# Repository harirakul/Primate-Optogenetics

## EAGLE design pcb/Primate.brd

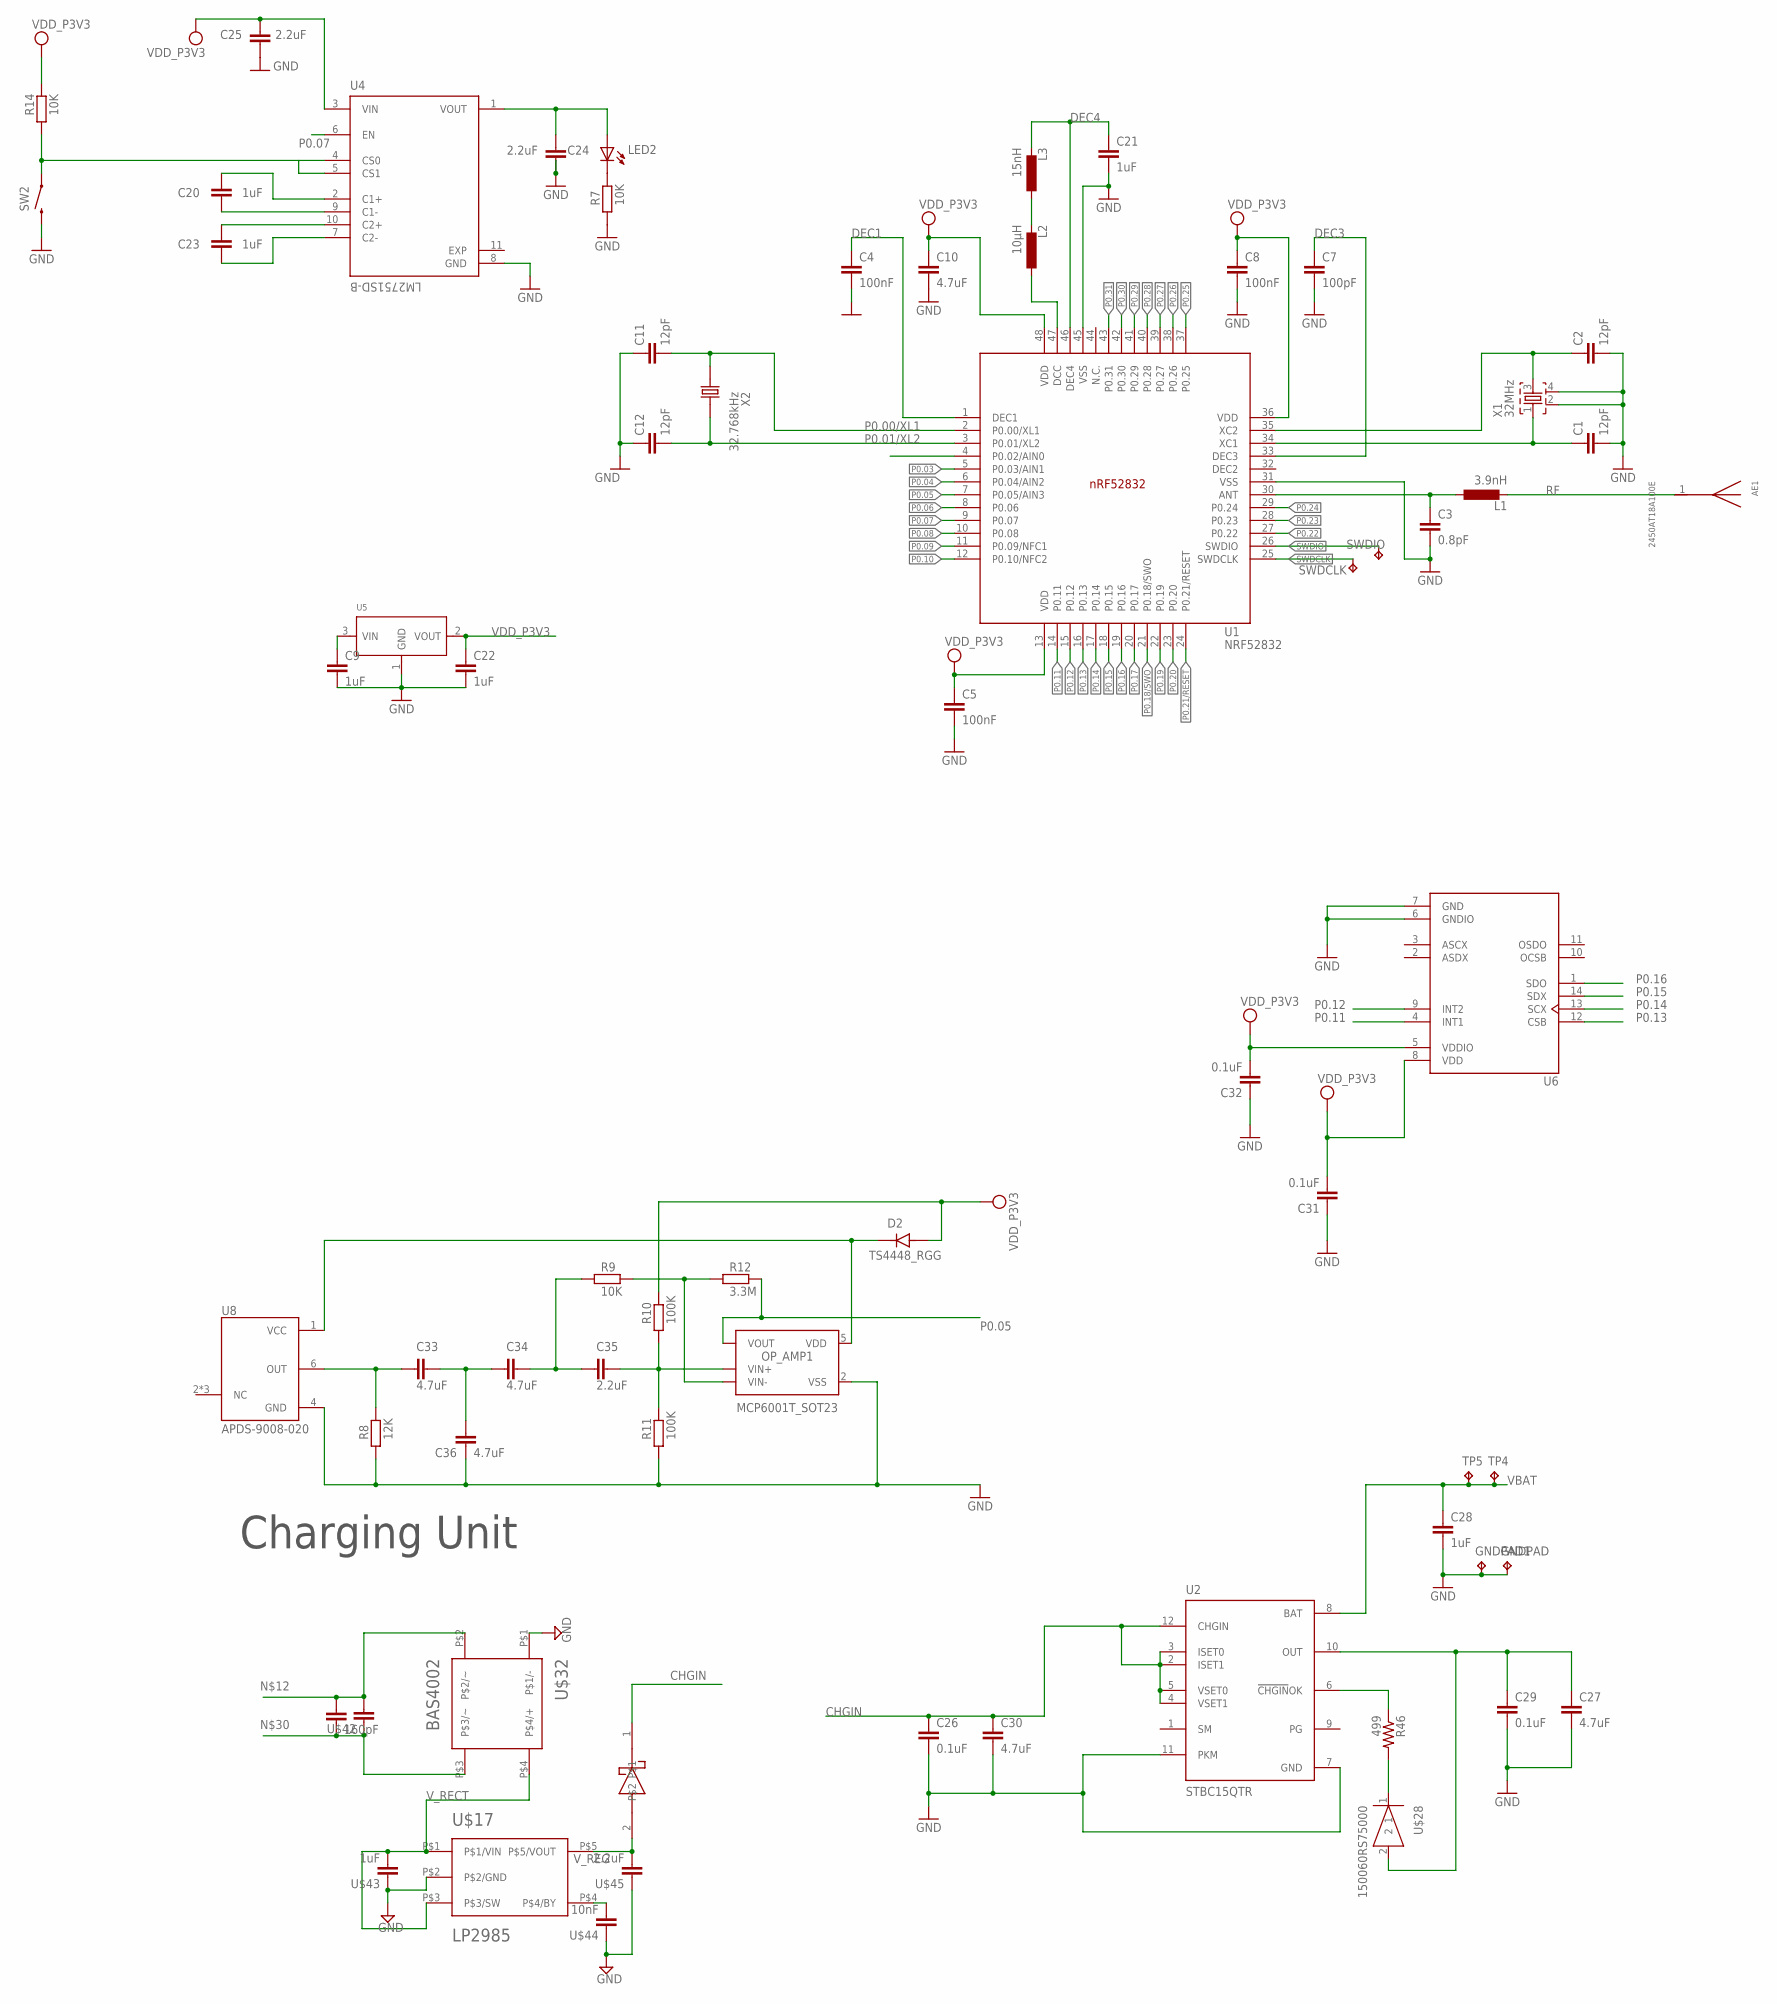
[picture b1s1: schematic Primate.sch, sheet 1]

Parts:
AE1: 2450AT18A100E; ANTC3216X140N
C1, C2, C11, C12: 12pF; C0201
C3: 0.8pF; C0201
C4, C5, C8: 100nF; C0201
C7: 100pF; C0201
C9, C20, C21, C22, C23, C28: 1uF; C0201
C10, C27, C30, C33, C34, C36: 4.7uF; C0402
C24, C25, C35: 2.2uF; C0402
C26, C29, C31, C32: 0.1uF; C0201
D2: TS4448_RGG; DIO_TS4448_RGG
GNDPAD, GNDPAD1: TPTP20SQ; TP20SQ
L1: 3.9nH; L0201
L2: 10µH; L0201
L3: 15nH; L0201
LED2: LEDCHIPLED_0805; CHIPLED_0805
OP_AMP1: MCP6001T_SOT23; SOT95P280X145-5N
R7, R9, R14: 10K; R0603
R8: 12K; R0603
R10, R11: 100K; R0603
R12: 3.3M; R0603
R46: 499; R0201
SW2: RS032G05A3SM-SPST-MOMENTARY-SWSMD-1101NE; TACTILE-SWITCH-1101NE
SWDCLK: TPB1,27; B1,27
SWDIO: TPB1,27; B1,27
TP4, TP5: TPTP20SQ; TP20SQ
U1: NRF52832; QFN40P600X600X90-48_N
U2: STBC15QTR; QFN40P200X170X55-12N
U4: LM2751SD-B; SON50P300X300X80-11N
U5: PMIC-LDO-XC6206P302MR(SOT23); SOT-23
U6: BMI160; PQFN50P250X300X88-14N
U8: APDS-9008-020; XDCR_APDS-9008-020
U$17: LP2985; SOT-23
U$28: 150060RS75000
U$32: BAS4002; SOT143
U$41: 160pF; C0201
U$42: 5pF; C0201
U$43: 1uF; C0201
U$44: 10nF; C0201
U$45: 2.2uF; C0201
U$46: CDBQC0130L-HF; 0402DIODE
X1: 32MHz; BT-XTAL_2016_N
X2: 32.768kHz; XTAL_ECS-.327-7-12-TR

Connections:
ANT: C3.1, L1.1, U1.30 (ANT)
CHGIN: C26.1, C30.1, U2.2 (ISET1), U2.3 (ISET0), U2.4 (VSET1), U2.5 (VSET0), U2.12 (CHGIN), U$46.1
DEC1: C4.1, U1.1 (DEC1)
DEC3: C7.1, U1.33 (DEC3)
DEC4: C21.1, L3.2, U1.46 (DEC4)
EXP: U4.11 (EXP)
GND: C1.2, C2.2, C3.2, C4.2, C5.2, C7.2, C8.2, C9.2, C10.2, C11.1, C12.1, C21.2, C22.2, C24.2, C25.2, C26.2, C27.2, C28.2, C29.2, C30.2, C31.1, C32.1, C36.2, GNDPAD.TP, GNDPAD1.TP, OP_AMP1.2 (VSS), R7.1, R8.1, R11.1, SW2.2, U1.31 (VSS), U1.45 (VSS), U2.7 (GND), U2.11 (PKM), U4.8 (GND), U5.1 (GND), U6.6 (GNDIO), U6.7 (GND), U8.4 (GND), U$17.P$2 (P$2/GND), U$32.P$1 (P$1/-), U$43.1, U$44.1, U$45.1, X1.2, X1.4
unnamed: L2.2, L3.1
unnamed: C2.1, U1.35 (XC2), X1.3
unnamed: L2.1, U1.47 (DCC)
unnamed: U$32.P$2 (P$2/~), U$41.1, U$42.2
unnamed: R46.2, U$28.1
unnamed: C33.2, R8.2, U8.6 (OUT)
unnamed: C27.1, C29.1, U2.10 (OUT), U$28.2
unnamed: R46.1, U2.6 (!CHGIN!OK)
unnamed: U$32.P$3 (P$3/~), U$41.2, U$42.1
unnamed: U$17.P$4 (P$4/BY), U$44.2
unnamed: C20.1, U4.2 (C1+)
unnamed: C20.2, U4.9 (C1-)
unnamed: C23.1, U4.10 (C2+)
unnamed: C24.1, LED2.A, U4.1 (VOUT)
unnamed: C23.2, U4.7 (C2-)
unnamed: C33.1, C34.2, C36.1
unnamed: LED2.C, R7.2
unnamed: C34.1, C35.2, R9.1
unnamed: D2.C (K), OP_AMP1.5 (VDD), U8.1 (VCC)
unnamed: C35.1, OP_AMP1.3 (VIN+), R10.1, R11.2
unnamed: OP_AMP1.4 (VIN-), R9.2, R12.1
unnamed: U4.4 (CS0), U4.5 (CS1)
unnamed: R14.1, SW2.1
OUT: U1.4 (P0.02/AIN0)
P0.00/XL1: C11.2, U1.2 (P0.00/XL1), X2.1
P0.01/XL2: C12.2, U1.3 (P0.01/XL2), X2.2
P0.03: U1.5 (P0.03/AIN1)
P0.04: U1.6 (P0.04/AIN2)
P0.05: OP_AMP1.1 (VOUT), R12.2, U1.7 (P0.05/AIN3)
P0.06: U1.8 (P0.06)
P0.07: U1.9 (P0.07), U4.6 (EN)
P0.08: U1.10 (P0.08)
P0.09: U1.11 (P0.09/NFC1)
P0.10: U1.12 (P0.10/NFC2)
P0.11: U1.14 (P0.11), U6.4 (INT1)
P0.12: U1.15 (P0.12), U6.9 (INT2)
P0.13: U1.16 (P0.13), U6.12 (CSB)
P0.14: U1.17 (P0.14), U6.13 (SCX)
P0.15: U1.18 (P0.15), U6.14 (SDX)
P0.16: U1.19 (P0.16), U6.1 (SDO)
P0.17: U1.20 (P0.17)
P0.18/SWO: U1.21 (P0.18/SWO)
P0.19: U1.22 (P0.19)
P0.20: U1.23 (P0.20)
P0.21/RESET: U1.24 (P0.21/RESET)
P0.22: U1.27 (P0.22)
P0.23: U1.28 (P0.23)
P0.24: U1.29 (P0.24)
P0.25: U1.37 (P0.25)
P0.26: U1.38 (P0.26)
P0.27: U1.39 (P0.27)
P0.28: U1.40 (P0.28)
P0.29: U1.41 (P0.29)
P0.30: U1.42 (P0.30)
P0.31: U1.43 (P0.31)
RF: AE1.1, L1.2
SWDCLK: SWDCLK.TP, U1.25 (SWDCLK)
SWDIO: SWDIO.TP, U1.26 (SWDIO)
VBAT: C28.1, TP4.TP, TP5.TP, U2.8 (BAT)
VBAT1: C9.1, U5.3 (VIN)
VDD_P3V3: C5.1, C8.1, C10.1, C22.1, C25.1, C31.2, C32.2, D2.A, R10.2, R14.2, U1.13 (VDD), U1.36 (VDD), U1.48 (VDD), U4.3 (VIN), U5.2 (VOUT), U6.5 (VDDIO), U6.8 (VDD)
V_RECT: U$17.P$1 (P$1/VIN), U$17.P$3 (P$3/SW), U$32.P$4 (P$4/+), U$43.2
V_REG: U$17.P$5 (P$5/VOUT), U$45.2, U$46.2
X1: C1.1, U1.34 (XC1), X1.1

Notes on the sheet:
Charging Unit

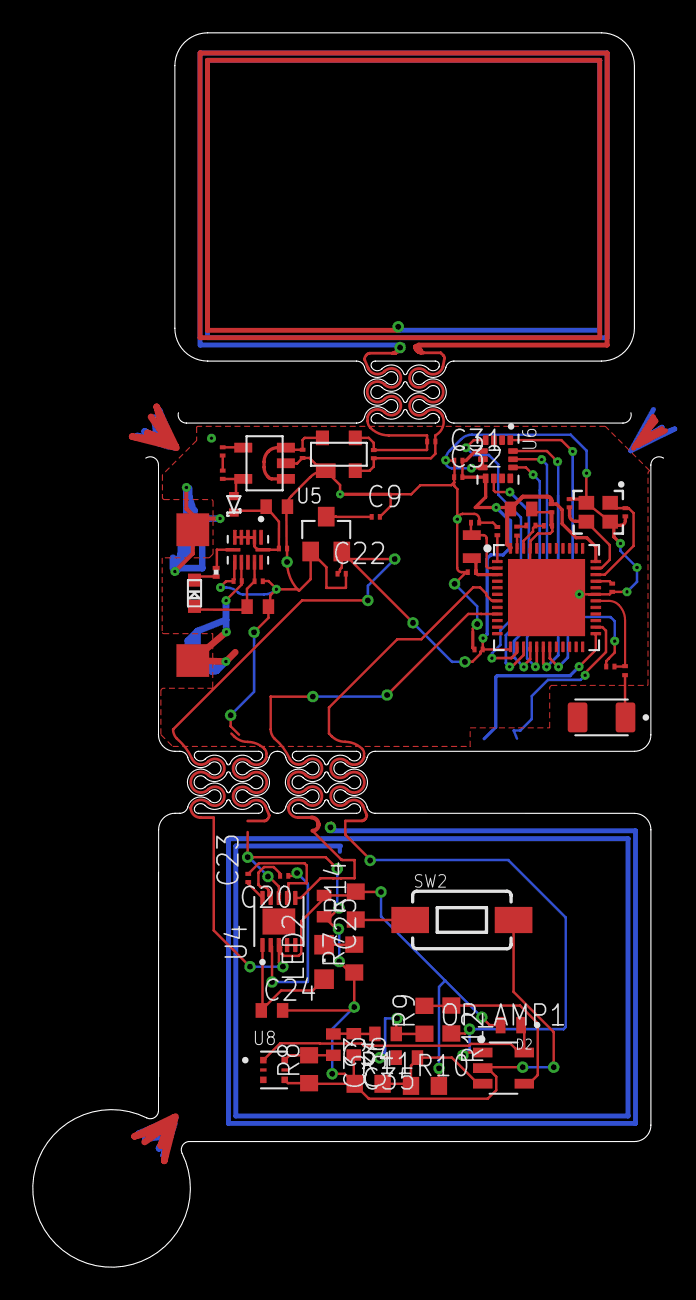
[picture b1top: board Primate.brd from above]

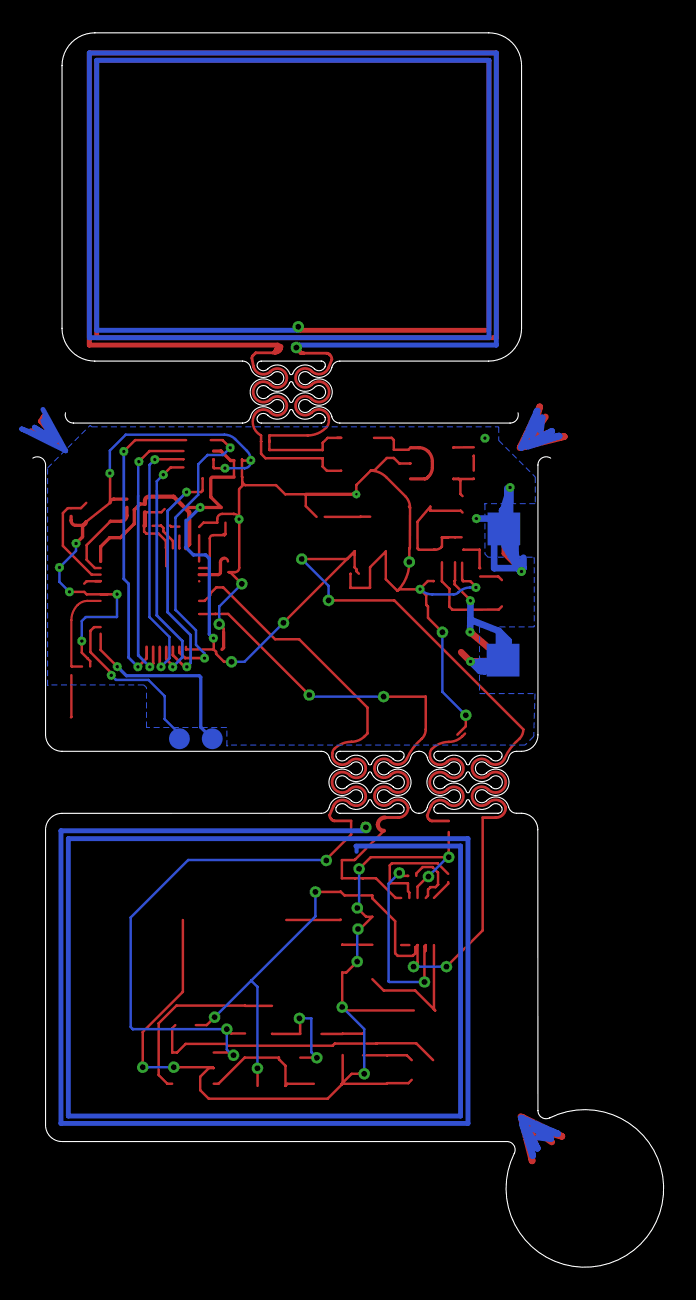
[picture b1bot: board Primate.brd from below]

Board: 2 copper layers, 38.4 x 75.2 mm, 67 parts (4 on the bottom side), 48 nets.

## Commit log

2023-02-14 added ADC
2023-02-15 added led advertising
2023-02-20 added bluetooth and blinky
2023-02-21 Added Flutter app source code
2023-02-28 added pcb
2023-02-28 Added Bluetooth pairing feature to app
2023-03-01 Revert to original BLE code
2023-03-02 Added BLE characteristics and turning LED on
2023-03-03 LED control over BLE working
2023-03-03 Controlling LED via GPIO
2023-03-09 downgraded SDK to 15.0.0
2023-03-13 added single-ended mode
2023-03-14 added adc bluetooth with UART
2023-03-14 Added Bluetooth scanning feature to app
2023-03-14 Added disconnect feature to app
2023-03-18 Integrated lbs and nus service
2023-03-20 Added ADC reading and graphing feature to app
